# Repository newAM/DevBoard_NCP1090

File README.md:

## NCP1090 802.3af PoE Development board

This project is a development board for the NCP1090 802.3af power over Ethernet controller.

## Media

## Project Contents
-  DevBoard_NCP1090_KiCAD - KiCad PCB and schematic files
-  DevBoard_NCP1090_Media - photos

## Bill of Materials

| Reference | Value   | Package | Digikey P/N          | Quantity |
| --------- |---------|---------|----------------------|----------|
| D1-D2     | Bridge  | SMA     | MDB6SFSCT-ND         | 2        |
| D3        | SMAJ58A | MDB62   | SMAJ58A-E3/61GICT-ND | 1        |
| C1        | 100n    | 0805    | 1276-6840-1-ND       | 1        |
| R1        | 24.9k   | 0603    | 311-24.9KCRCT-ND     | 1        |
| R2        | 178k    | 0603    | 311-178KCRCT-ND      | 1        |
| R3        | 4420    | 0603    | 311-4.42KCRCT-ND     | 1        |
| X1        | 1x4     | 2.54mm  |                      | 1        |
| X2        | 1x3     | 2.54mm  |                      | 1        |

## Software Used
- [KiCad](http://kicad-pcb.org/) 5.0.0 release

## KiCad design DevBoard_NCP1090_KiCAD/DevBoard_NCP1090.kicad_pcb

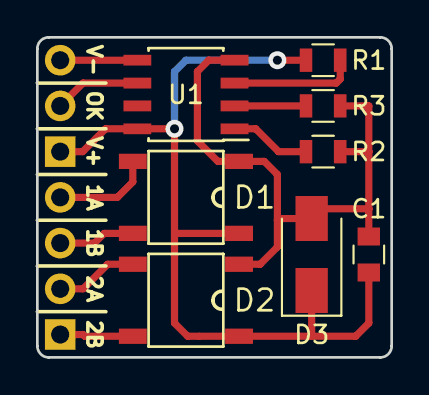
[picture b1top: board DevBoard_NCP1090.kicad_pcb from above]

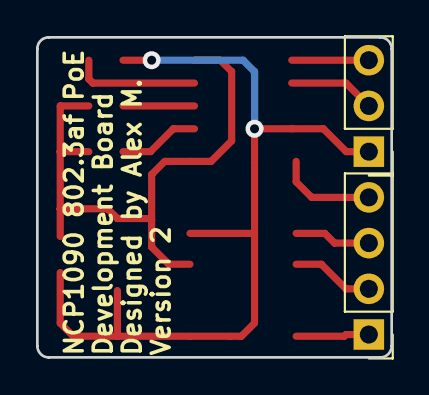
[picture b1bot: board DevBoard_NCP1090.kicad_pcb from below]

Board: 2 copper layers, 19.7 x 17.8 mm, 10 parts (2 on the bottom side), 11 nets.

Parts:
C1: 100n; C_0805
D1, D2: MDB6S; Micro-DIP-4
D3: SMAJ58A; D_SMA
R1: 24.9k; R_0805
R2: 178k; R_0805
R3: 4420; R_0805
U1: NCP1090; SOIC-8_3.9x4.9mm_Pitch1.27mm
X1: Conn_01x04; Pin_Header_Straight_1x04_Pitch2.54mm
X2: Conn_01x03; Pin_Header_Straight_1x03_Pitch2.54mm

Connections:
/BR1a: D1.3, X1.4
/BR1b: D1.4, X1.3
/BR2a: D2.3, X1.2
/BR2b: D2.4, X1.1
/N: C1.2, D1.2, D2.2, D3.2, R2.1, R3.1, U1.4
/P: C1.1, D1.1, D2.1, D3.1, R1.2, U1.8, X2.1
/PGOOD: U1.6, X2.2
/RTN: U1.5, X2.3
unnamed: R1.1, U1.3
unnamed: R2.2, U1.1
unnamed: R3.2, U1.2

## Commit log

2018-09-09 v1 commit
2018-09-09 v2 initial commit
2018-10-09 added media
